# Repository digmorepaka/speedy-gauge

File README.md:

# An ATMEGA328P-based multi-instrument gauge module for Speeduino ECUs

## Demo
[YouTube Video](https://youtu.be/gbWBmTSCocg)

## Images

## TODO
* Display quality, I will be testing ST7798 IPS displays for their low temperature response
* Detailed README
* Better data acquisition
* Support for use as AUX GPIO

communication used from https://github.com/sbtoonz/Speeduino-Oled-Display

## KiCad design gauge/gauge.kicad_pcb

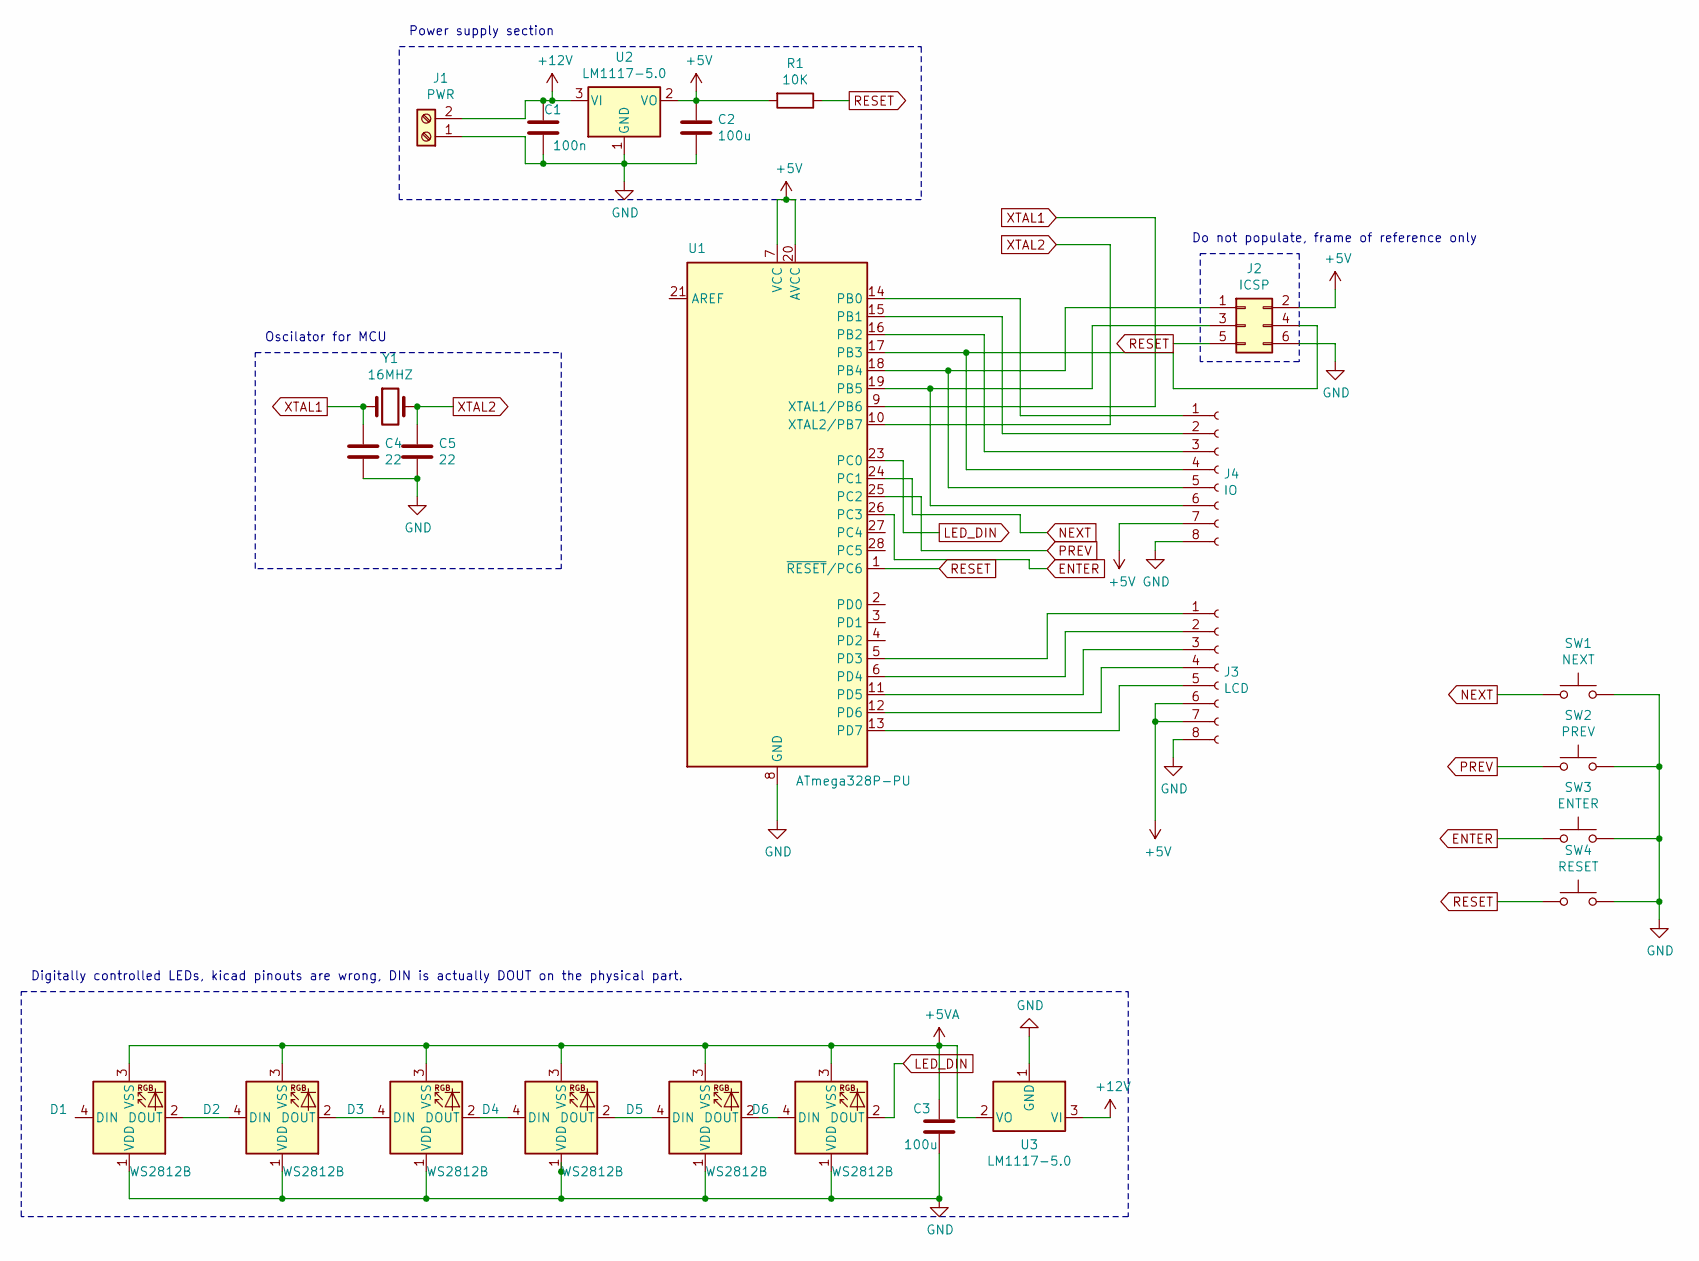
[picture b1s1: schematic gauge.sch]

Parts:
C1: 100n; C_1210_3225Metric_Pad1.42x2.65mm_HandSolder
C2, C3: 100u; C_1210_3225Metric_Pad1.42x2.65mm_HandSolder
C4, C5: 22; C_Disc_D3.0mm_W1.6mm_P2.50mm
D1, D2, D3, D4, D5, D6: WS2812B; LED_WS2812B_PLCC4_5.0x5.0mm_P3.2mm
J1: PWR; TerminalBlock_bornier-2_P5.08mm
J2: ICSP; PinHeader_2x03_P2.54mm_Vertical
J3: LCD; PinHeader_1x08_P2.54mm_Vertical
J4: IO; PinHeader_1x08_P2.54mm_Vertical
R1: 10K; R_0402_1005Metric
SW1: NEXT; SW_PUSH_6mm_H4.3mm
SW2: PREV; SW_PUSH_6mm_H4.3mm
SW3: ENTER; SW_PUSH_6mm_H4.3mm
SW4: RESET; SW_PUSH_6mm_H4.3mm
U1: ATmega328P-PU; DIP-28_W7.62mm
U2, U3: LM1117-5.0; SOT-223-3_TabPin2
Y1: 16MHZ; Crystal_HC49-U_Vertical

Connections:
+5V: C2.1, J2.2, J3.6, J3.7, J4.7, R1.2, U1.7 (VCC), U1.20 (AVCC), U2.2 (VO)
+5VA: C3.1, D1.3 (VSS), D2.3 (VSS), D3.3 (VSS), D4.3 (VSS), D5.3 (VSS), D6.3 (VSS), U3.2 (VO)
+12V: C1.1, J1.2, U2.3 (VI), U3.3 (VI)
ENTER: SW3.1, U1.26 (PC3)
GND: C1.2, C2.2, C3.2, C4.2, C5.2, D1.1 (VDD), D2.1 (VDD), D3.1 (VDD), D4.1 (VDD), D5.1 (VDD), D6.1 (VDD), J1.1, J2.6, J3.8, J4.8, SW1.2, SW2.2, SW3.2, SW4.2, U1.8 (GND), U1.22 (GND), U2.1 (GND), U3.1 (GND)
LED_DIN: D6.2 (DOUT), U1.23 (PC0)
NEXT: SW1.1, U1.24 (PC1)
unnamed: D1.2 (DOUT), D2.4 (DIN)
unnamed: D2.2 (DOUT), D3.4 (DIN)
unnamed: D3.2 (DOUT), D4.4 (DIN)
unnamed: D4.2 (DOUT), D5.4 (DIN)
unnamed: D5.2 (DOUT), D6.4 (DIN)
unnamed: J2.1, J4.5, U1.18 (PB4)
unnamed: J2.3, J4.6, U1.19 (PB5)
unnamed: J2.4, J4.4, U1.17 (PB3)
unnamed: J3.1, U1.5 (PD3)
unnamed: J3.2, U1.6 (PD4)
unnamed: J3.3, U1.11 (PD5)
unnamed: J3.4, U1.12 (PD6)
unnamed: J3.5, U1.13 (PD7)
unnamed: J4.1, U1.14 (PB0)
unnamed: J4.2, U1.15 (PB1)
unnamed: J4.3, U1.16 (PB2)
PREV: SW2.1, U1.25 (PC2)
RESET: J2.5, R1.1, SW4.1, U1.1 (~RESET~/PC6)
XTAL1: C4.1, U1.9 (XTAL1/PB6), Y1.1
XTAL2: C5.1, U1.10 (XTAL2/PB7), Y1.2

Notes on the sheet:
Digitally controlled LEDs, kicad pinouts are wrong, DIN is actually DOUT on the physical part.
Oscilator for MCU
Do not populate, frame of reference only
Power supply section

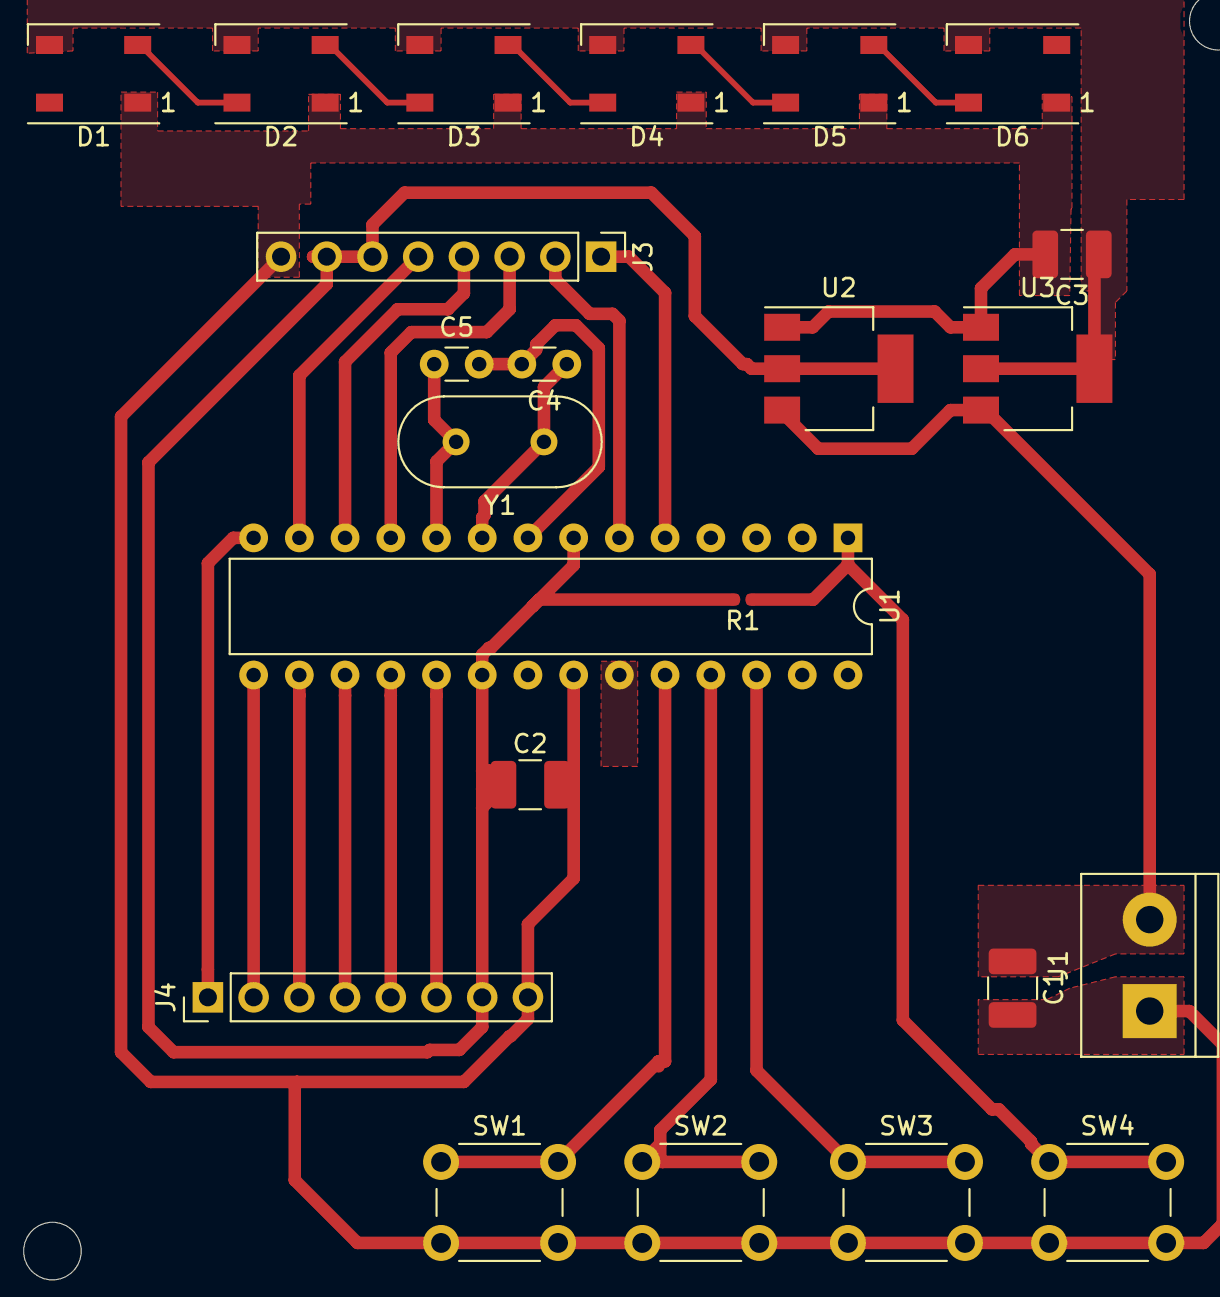
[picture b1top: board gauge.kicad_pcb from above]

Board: 2 copper layers, 23 parts (0 on the bottom side), 27 nets.

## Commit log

2020-12-01 Initial
2020-12-02 Rename gauge_test.ino to gauge_5110_WS2812B.ino
2020-12-02 add pdf
2020-12-02 fix schematic
